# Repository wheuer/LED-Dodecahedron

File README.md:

# LED-Dodecahedron

This repository tracks the most recent state of my LED dodecahedron project.

It's a mess and unpolished. For a more in depth look at the project and it's history see [my website](https://www.williamfheuer.com/project-portfolio).

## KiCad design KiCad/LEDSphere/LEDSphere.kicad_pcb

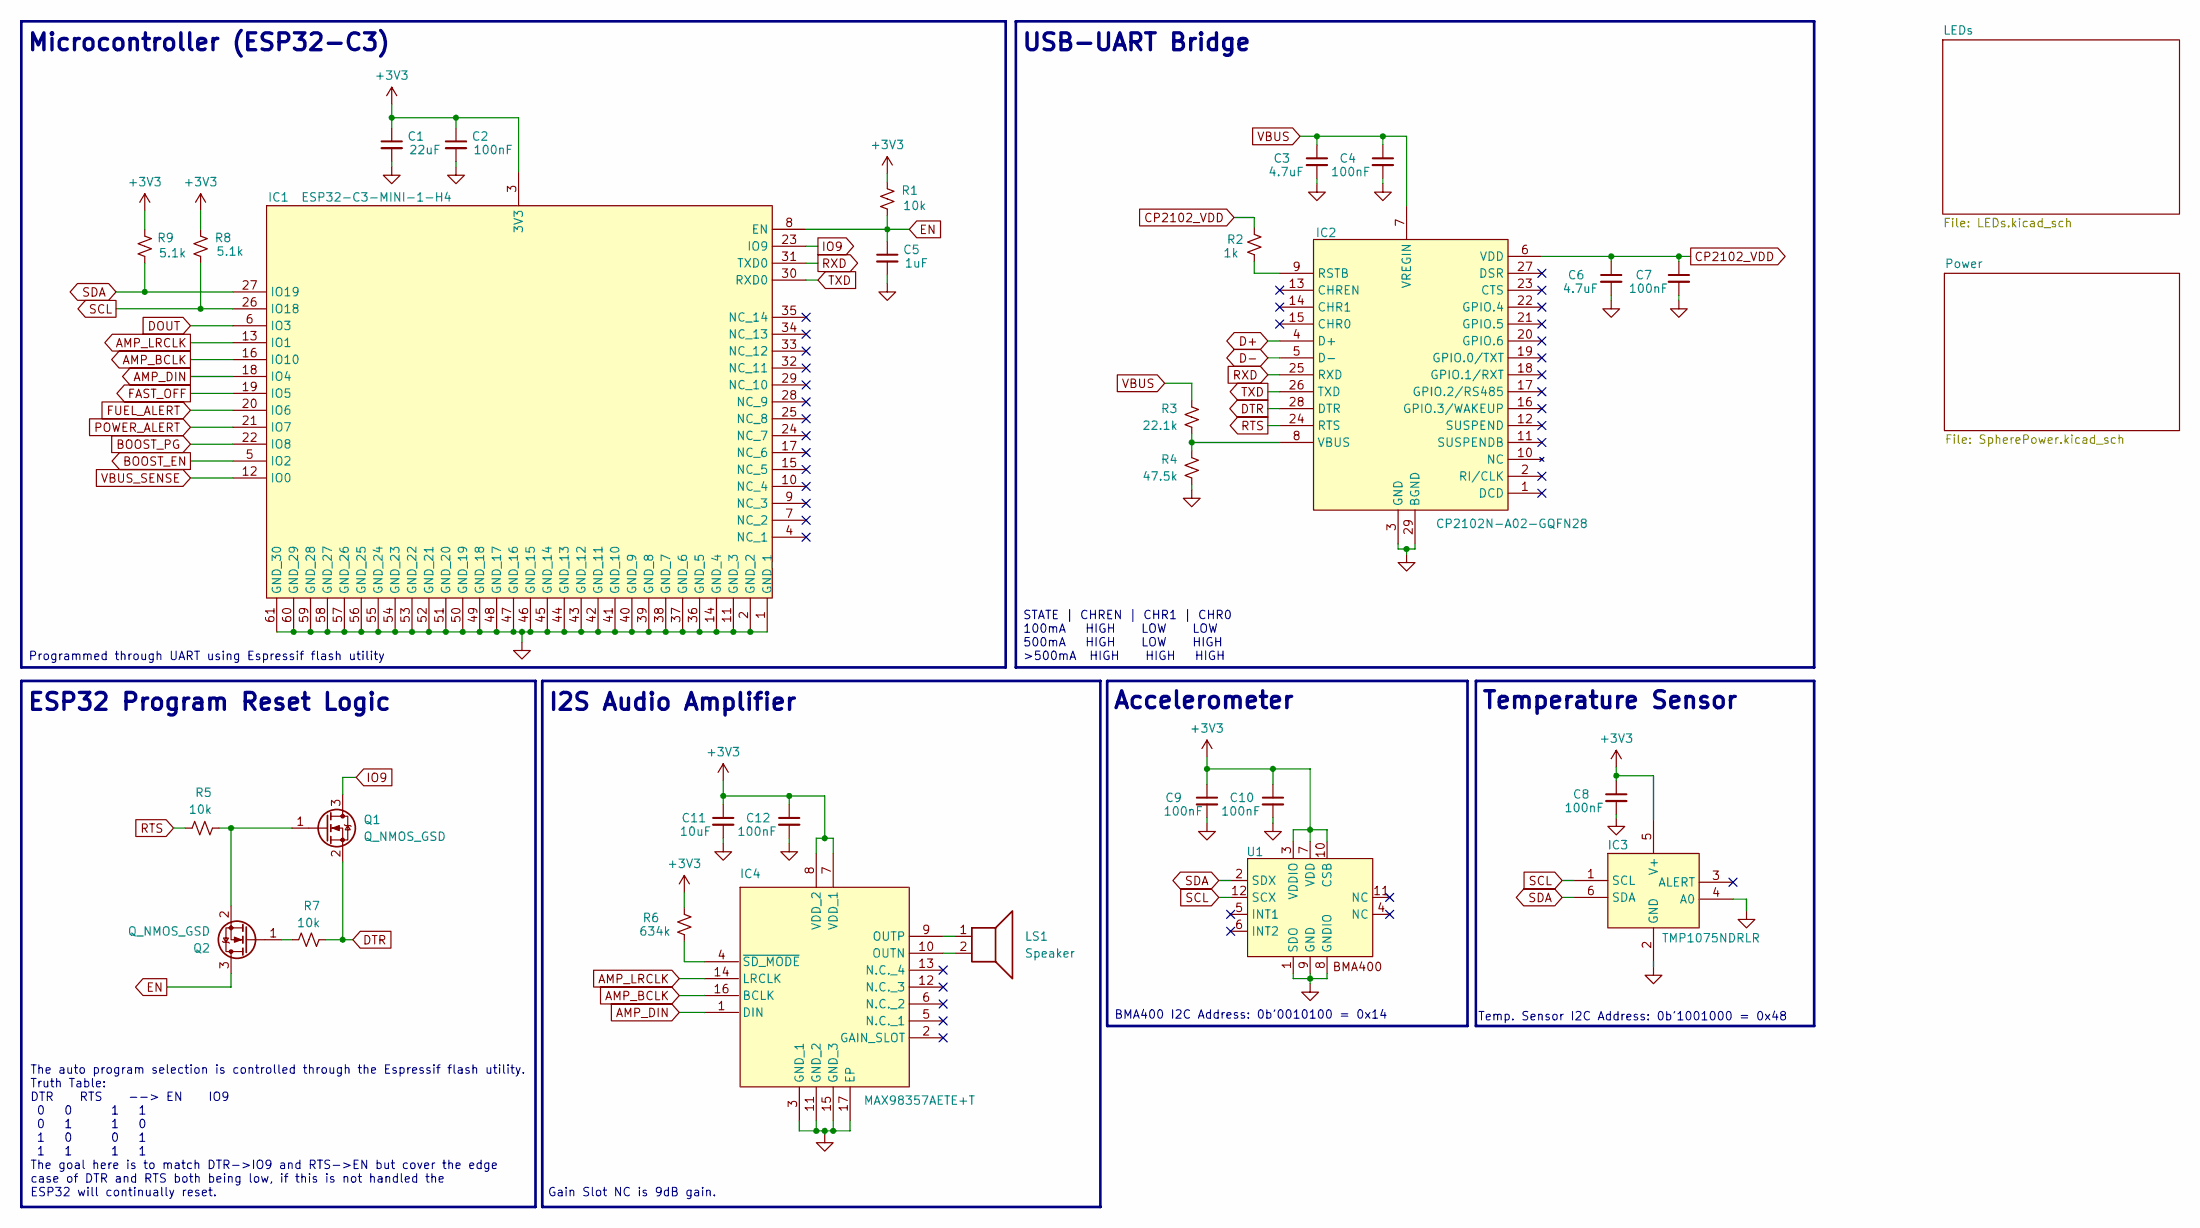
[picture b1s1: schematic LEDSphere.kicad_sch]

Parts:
C1: 22uF; C_0603_1608Metric
C2, C4, C7, C8, C9, C10, C12: 100nF; C_0402_1005Metric
C3, C6: 4.7uF; C_0402_1005Metric
C5: 1uF; C_0402_1005Metric
C11: 10uF; C_0603_1608Metric
IC1: ESP32-C3-MINI-1-H4; ESP32C3MINI1H4; Mouser Part Number 356-ESP32-C3-MINI1H4
IC2: CP2102N-A02-GQFN28; cp2102_QFN50P500X500X80-29N-D; Mouser Part Number 634-CP2102NA02GQFN28
IC3: TMP1075NDRLR; SOTFL50P160X60-6N; Mouser Part Number 595-TMP1075NDRLR
IC4: MAX98357AETE+T; QFN50P300X300X80-17N; Mouser Part Number 700-MAX98357AETE+T
LS1: Speaker; speakerPads
Q1, Q2: Q_NMOS_GSD; NMOS_SOT91P240X110-3N
R1, R5, R7: 10k; R_0402_1005Metric
R2: 1k; R_0402_1005Metric
R3: 22.1k; R_0402_1005Metric
R4: 47.5k; R_0402_1005Metric
R6: 634k; R_0402_1005Metric
R8, R9: 5.1k; R_0402_1005Metric
U1: BOSCH_LGA-12

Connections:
+3V3: C1.1, C2.1, C8.1, C9.1, C10.1, C11.1, C12.1, IC1.3 (3V3), IC3.5 (V+), IC4.7 (VDD_1), IC4.8 (VDD_2), R1.2, R6.2, R8.2, R9.2, U1.3 (VDDIO), U1.7 (VDD), U1.10 (CSB); also elsewhere on the board
AMP_BCLK: IC1.16 (IO10), IC4.16 (BCLK)
AMP_DIN: IC1.18 (IO4), IC4.1 (DIN)
AMP_LRCLK: IC1.13 (IO1), IC4.14 (LRCLK)
BOOST_EN: IC1.5 (IO2); also elsewhere on the board
BOOST_PG: IC1.22 (IO8); also elsewhere on the board
CP2102_VDD: C6.1, C7.1, IC2.6 (VDD), R2.1
D+: IC2.4 (D+); also elsewhere on the board
D-: IC2.5 (D-); also elsewhere on the board
DOUT: IC1.6 (IO3); also elsewhere on the board
DTR: IC2.28 (DTR), Q1.2 (S), R7.1
EN: C5.1, IC1.8 (EN), Q2.3 (D), R1.1
FAST_OFF: IC1.19 (IO5); also elsewhere on the board
FUEL_ALERT: IC1.20 (IO6); also elsewhere on the board
GND: C1.2, C2.2, C3.2, C4.2, C5.2, C6.2, C7.2, C8.2, C9.2, C10.2, C11.2, C12.2, IC1.1 (GND_1), IC1.2 (GND_2), IC1.11 (GND_3), IC1.14 (GND_4), IC1.36 (GND_5), IC1.37 (GND_6), IC1.38 (GND_7), IC1.39 (GND_8), IC1.40 (GND_9), IC1.41 (GND_10), IC1.42 (GND_11), IC1.43 (GND_12), IC1.44 (GND_13), IC1.45 (GND_14), IC1.46 (GND_15), IC1.47 (GND_16), IC1.48 (GND_17), IC1.49 (GND_18), IC1.50 (GND_19), IC1.51 (GND_20), IC1.52 (GND_21), IC1.53 (GND_22), IC1.54 (GND_23), IC1.55 (GND_24), IC1.56 (GND_25), IC1.57 (GND_26), IC1.58 (GND_27), IC1.59 (GND_28), IC1.60 (GND_29), IC1.61 (GND_30), IC2.3 (GND), IC2.29 (BGND), IC3.2 (GND), IC3.4 (A0), IC4.3 (GND_1), IC4.11 (GND_2), IC4.15 (GND_3), IC4.17 (EP), R4.2, U1.1 (SDO), U1.8 (GNDIO), U1.9 (GND); also elsewhere on the board
IO9: IC1.23 (IO9), Q1.3 (D)
unnamed: IC2.9 (RSTB), R2.2
unnamed: IC2.8 (VBUS), R3.2, R4.1
unnamed: IC4.10 (OUTN), LS1.2
unnamed: IC4.9 (OUTP), LS1.1
unnamed: IC4.4 (~SD_MODE), R6.1
unnamed: Q1.1 (G), Q2.2 (S), R5.1
unnamed: Q2.1 (G), R7.2
POWER_ALERT: IC1.21 (IO7); also elsewhere on the board
RTS: IC2.24 (RTS), R5.2
RXD: IC1.31 (TXD0), IC2.25 (RXD)
SCL: IC1.26 (IO18), IC3.1 (SCL), R8.1, U1.12 (SCX); also elsewhere on the board
SDA: IC1.27 (IO19), IC3.6 (SDA), R9.1, U1.2 (SDX); also elsewhere on the board
TXD: IC1.30 (RXD0), IC2.26 (TXD)
VBUS: C3.1, C4.1, IC2.7 (VREGIN), R3.1; also elsewhere on the board
VBUS_SENSE: IC1.12 (IO0); also elsewhere on the board

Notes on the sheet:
I2S Audio Amplifier
Gain Slot NC is 9dB gain.
Temperature Sensor
Microcontroller (ESP32-C3)
Programmed through UART using Espressif flash utility
BMA400 I2C Address: 0b'0010100 = 0x14
The auto program selection is controlled through the Espressif flash utility. Truth Table: DTR RTS --> EN IO9 0 0 1 1 0 1 1 0 1 0 0 1 1 1 1 1 The goal here is to match DTR->IO9 and RTS->EN but cover the edge case of DTR and RTS both being low, if this is not handled the ESP32 will continually reset.
STATE | CHREN | CHR1 | CHR0 100mA HIGH LOW LOW 500mA HIGH LOW HIGH >500mA HIGH HIGH HIGH
Temp. Sensor I2C Address: 0b'1001000 = 0x48
Accelerometer
USB-UART Bridge
ESP32 Program Reset Logic

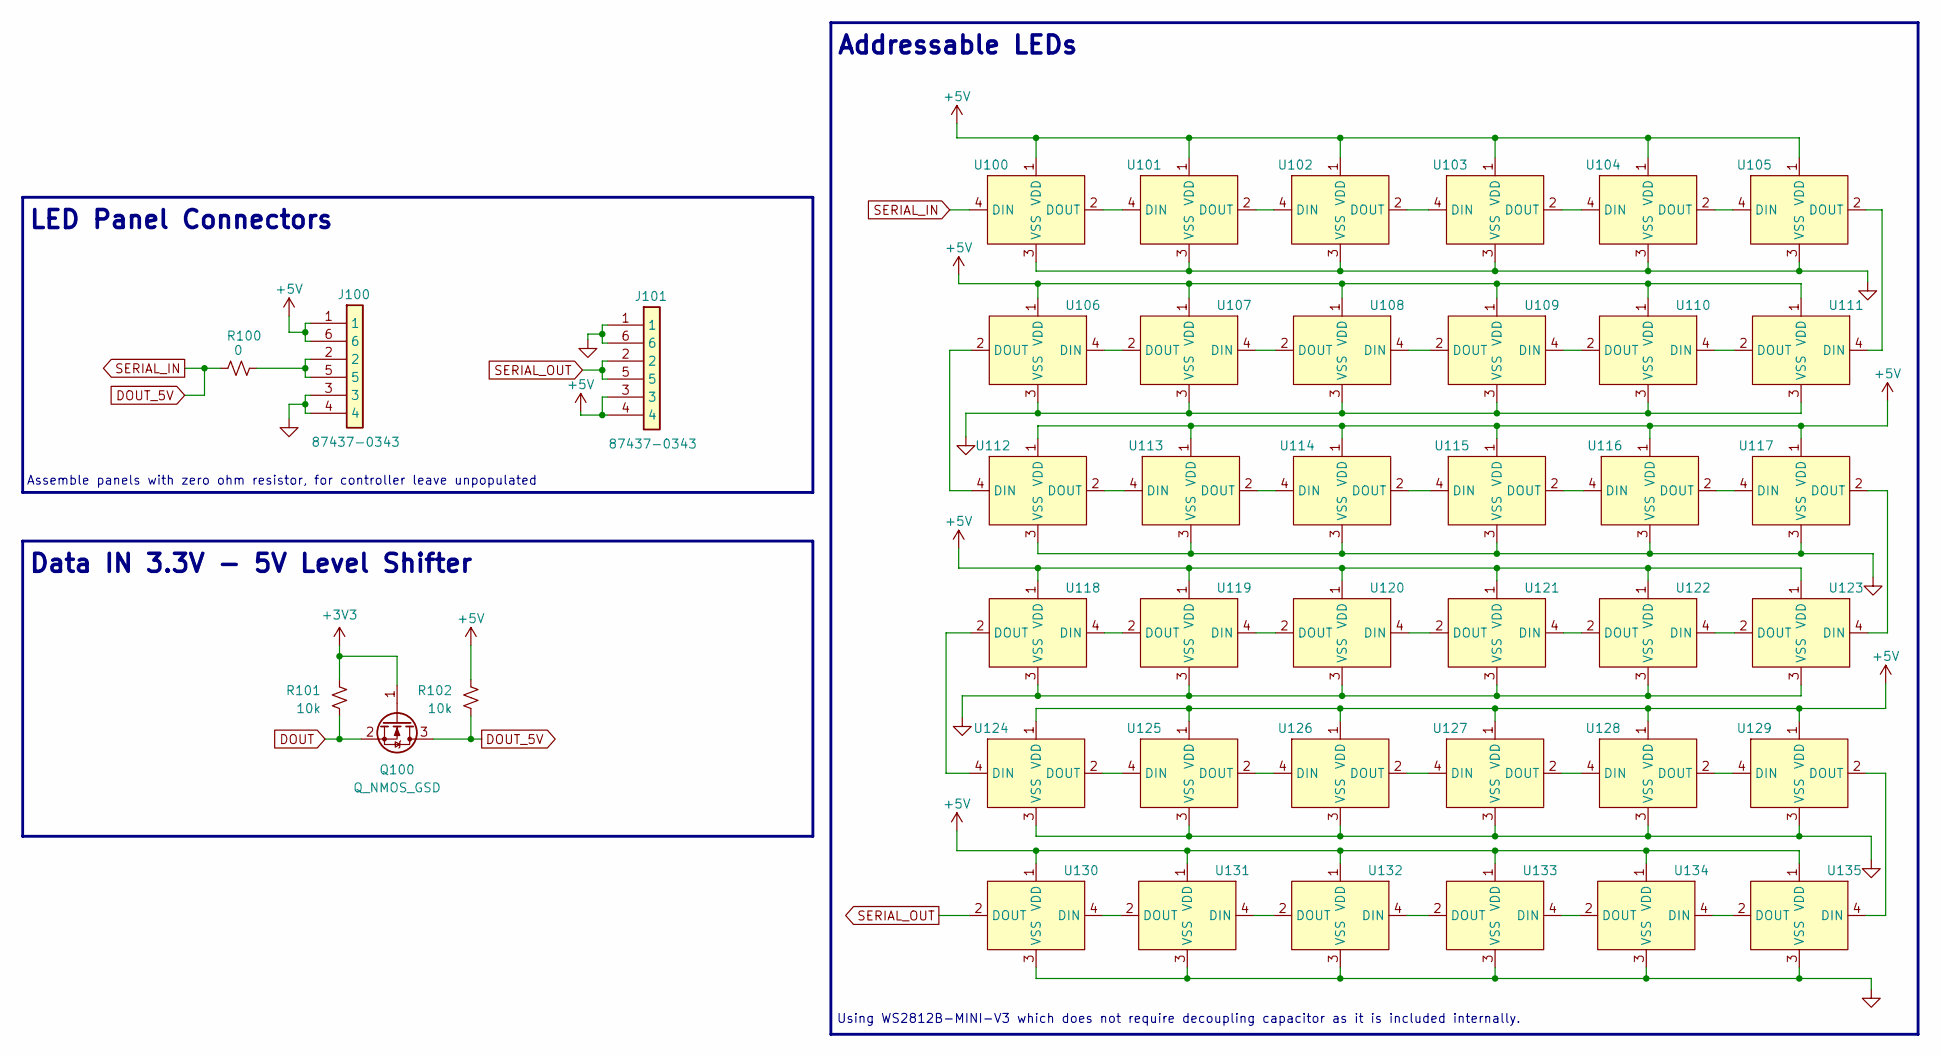
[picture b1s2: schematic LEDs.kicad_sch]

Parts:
J100, J101: 87437-0343; 874370343; Mouser Part Number 538-87437-0343
Q100: Q_NMOS_GSD; NMOS_SOT91P240X110-3N
R100: 0; R_0402_1005Metric
R101, R102: 10k; R_0402_1005Metric
U100, U101, U102, U103, U104, U105, U106, U107, U108, U109, U110, U111, U112, U113, U114, U115, U116, U117, U118, U119, U120, U121, U122, U123, U124, U125, U126, U127, U128, U129, U130, U131, U132, U133, U134, U135: WS2812-W-MINI

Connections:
+3V3: Q100.1 (G), R101.1; also elsewhere on the board
+5V: J100.1, J100.6, J101.3, J101.4, R102.1, U100.1 (VDD), U101.1 (VDD), U102.1 (VDD), U103.1 (VDD), U104.1 (VDD), U105.1 (VDD), U106.1 (VDD), U107.1 (VDD), U108.1 (VDD), U109.1 (VDD), U110.1 (VDD), U111.1 (VDD), U112.1 (VDD), U113.1 (VDD), U114.1 (VDD), U115.1 (VDD), U116.1 (VDD), U117.1 (VDD), U118.1 (VDD), U119.1 (VDD), U120.1 (VDD), U121.1 (VDD), U122.1 (VDD), U123.1 (VDD), U124.1 (VDD), U125.1 (VDD), U126.1 (VDD), U127.1 (VDD), U128.1 (VDD), U129.1 (VDD), U130.1 (VDD), U131.1 (VDD), U132.1 (VDD), U133.1 (VDD), U134.1 (VDD), U135.1 (VDD); also elsewhere on the board
DOUT: Q100.2 (S), R101.2; also elsewhere on the board
DOUT_5V: Q100.3 (D), R100.1, R102.2, U100.4 (DIN)
GND: J100.3, J100.4, J101.1, J101.6, U100.3 (VSS), U101.3 (VSS), U102.3 (VSS), U103.3 (VSS), U104.3 (VSS), U105.3 (VSS), U106.3 (VSS), U107.3 (VSS), U108.3 (VSS), U109.3 (VSS), U110.3 (VSS), U111.3 (VSS), U112.3 (VSS), U113.3 (VSS), U114.3 (VSS), U115.3 (VSS), U116.3 (VSS), U117.3 (VSS), U118.3 (VSS), U119.3 (VSS), U120.3 (VSS), U121.3 (VSS), U122.3 (VSS), U123.3 (VSS), U124.3 (VSS), U125.3 (VSS), U126.3 (VSS), U127.3 (VSS), U128.3 (VSS), U129.3 (VSS), U130.3 (VSS), U131.3 (VSS), U132.3 (VSS), U133.3 (VSS), U134.3 (VSS), U135.3 (VSS); also elsewhere on the board
unnamed: J100.2, J100.5, R100.2
unnamed: U100.2 (DOUT), U101.4 (DIN)
unnamed: U101.2 (DOUT), U102.4 (DIN)
unnamed: U102.2 (DOUT), U103.4 (DIN)
unnamed: U103.2 (DOUT), U104.4 (DIN)
unnamed: U104.2 (DOUT), U105.4 (DIN)
unnamed: U105.2 (DOUT), U111.4 (DIN)
unnamed: U106.4 (DIN), U107.2 (DOUT)
unnamed: U106.2 (DOUT), U112.4 (DIN)
unnamed: U107.4 (DIN), U108.2 (DOUT)
unnamed: U108.4 (DIN), U109.2 (DOUT)
unnamed: U109.4 (DIN), U110.2 (DOUT)
unnamed: U110.4 (DIN), U111.2 (DOUT)
unnamed: U112.2 (DOUT), U113.4 (DIN)
unnamed: U113.2 (DOUT), U114.4 (DIN)
unnamed: U114.2 (DOUT), U115.4 (DIN)
unnamed: U115.2 (DOUT), U116.4 (DIN)
unnamed: U116.2 (DOUT), U117.4 (DIN)
unnamed: U117.2 (DOUT), U123.4 (DIN)
unnamed: U118.4 (DIN), U119.2 (DOUT)
unnamed: U118.2 (DOUT), U124.4 (DIN)
unnamed: U119.4 (DIN), U120.2 (DOUT)
unnamed: U120.4 (DIN), U121.2 (DOUT)
unnamed: U121.4 (DIN), U122.2 (DOUT)
unnamed: U122.4 (DIN), U123.2 (DOUT)
unnamed: U124.2 (DOUT), U125.4 (DIN)
unnamed: U125.2 (DOUT), U126.4 (DIN)
unnamed: U126.2 (DOUT), U127.4 (DIN)
unnamed: U127.2 (DOUT), U128.4 (DIN)
unnamed: U128.2 (DOUT), U129.4 (DIN)
unnamed: U129.2 (DOUT), U135.4 (DIN)
unnamed: U130.4 (DIN), U131.2 (DOUT)
unnamed: U131.4 (DIN), U132.2 (DOUT)
unnamed: U132.4 (DIN), U133.2 (DOUT)
unnamed: U133.4 (DIN), U134.2 (DOUT)
unnamed: U134.4 (DIN), U135.2 (DOUT)
SERIAL_OUT: J101.2, J101.5, U130.2 (DOUT)

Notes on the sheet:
LED Panel Connectors
Addressable LEDs
Data IN 3.3V - 5V Level Shifter
Assemble panels with zero ohm resistor, for controller leave unpopulated
Using WS2812B-MINI-V3 which does not require decoupling capacitor as it is included internally.

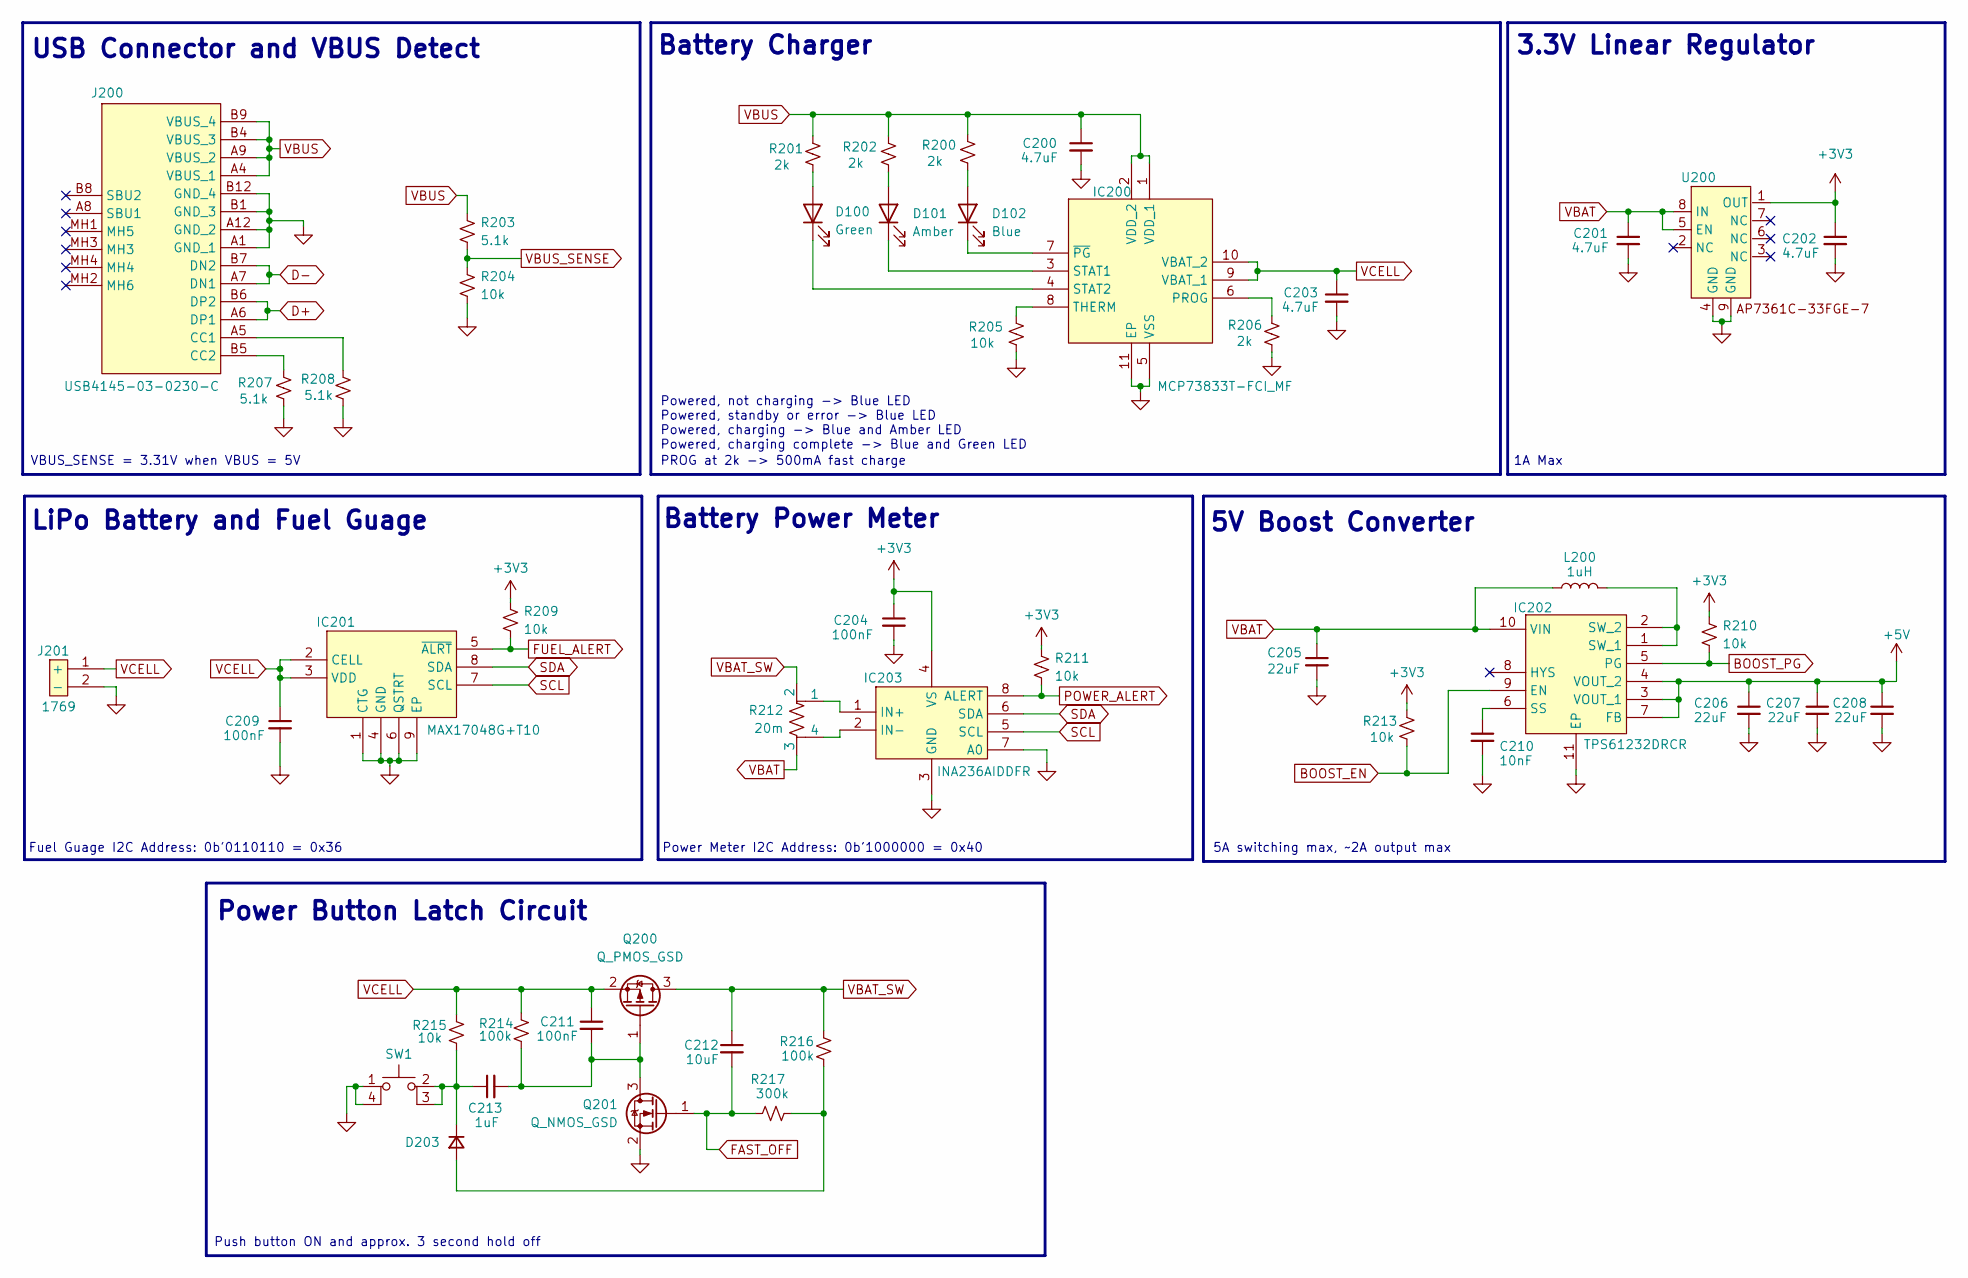
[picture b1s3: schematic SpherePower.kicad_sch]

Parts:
C200, C201, C202, C203: 4.7uF; C_0402_1005Metric
C204, C209, C211: 100nF; C_0402_1005Metric
C205, C206, C207, C208: 22uF; C_0603_1608Metric
C210: 10nF; C_0402_1005Metric
C212: 10uF; C_0603_1608Metric
C213: 1uF; C_0402_1005Metric
D100: Green; LED_0402_1005Metric
D101: Amber; LED_0402_1005Metric
D102: Blue; LED_0402_1005Metric
D203: D_Small; D_SOD-123F
IC200: MCP73833T-FCI_MF; batteryChg_SON50P300X300X100-11N-D; Mouser Part Number 579-MCP73833T-FCI/MF
IC201: MAX17048G+T10; SON50P200X200X80-9N-D; Mouser Part Number 700-MAX17048G+T10
IC202: TPS61232DRCR; boost_SON50P300X300X100-11N-D; Mouser Part Number 595-TPS61232DRCR
IC203: INA236AIDDFR; SOP65P280X110-8N; Mouser Part Number 595-INA236AIDDFR
J200: USB4145-03-0230-C; vertical_USB4145030230C; Mouser Part Number 640-USB4145-3-0230-C
J201: 1769; Mouser Part Number 485-1769
L200: 1uH; boostInductor_XFL4020
Q200: Q_PMOS_GSD; SSM3J332RLFT
Q201: Q_NMOS_GSD; NMOS_SOT91P240X110-3N
R200, R201, R202, R206: 2k; R_0402_1005Metric
R203, R207, R208: 5.1k; R_0402_1005Metric
R204, R205, R209, R210, R211, R213, R215: 10k; R_0402_1005Metric
R212: 20m; shunt_LVK12R020DER
R214, R216: 100k; R_0402_1005Metric
R217: 300k; R_0402_1005Metric
SW1: button_KMR_2
U200: linearReg_SON65P300X300X63-9N

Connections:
+3V3: C202.1, C204.1, IC203.4 (VS), R209.2, R210.2, R211.2, R213.2, U200.1 (OUT); also elsewhere on the board
+5V: C206.1, C207.1, C208.1, IC202.3 (VOUT_1), IC202.4 (VOUT_2), IC202.7 (FB); also elsewhere on the board
BOOST_EN: IC202.9 (EN), R213.1; also elsewhere on the board
BOOST_PG: IC202.5 (PG), R210.1; also elsewhere on the board
D+: J200.A6 (DP1), J200.B6 (DP2); also elsewhere on the board
D-: J200.A7 (DN1), J200.B7 (DN2); also elsewhere on the board
FAST_OFF: C212.2, Q201.1 (G), R217.2; also elsewhere on the board
FUEL_ALERT: IC201.5 (~ALRT), R209.1; also elsewhere on the board
GND: C200.2, C201.2, C202.2, C203.2, C204.2, C205.2, C206.2, C207.2, C208.2, C209.2, C210.2, IC200.5 (VSS), IC200.11 (EP), IC201.1 (CTG), IC201.4 (GND), IC201.6 (QSTRT), IC201.9 (EP), IC202.11 (EP), IC203.3 (GND), IC203.7 (A0), J200.A1 (GND_1), J200.A12 (GND_2), J200.B1 (GND_3), J200.B12 (GND_4), J201.2 (-), Q201.2 (S), R204.1, R205.1, R206.1, R207.1, R208.1, SW1.1, SW1.4, U200.4 (GND), U200.9 (GND); also elsewhere on the board
unnamed 18: R201.1; also elsewhere on the board
unnamed 19: IC200.4 (STAT2); also elsewhere on the board
unnamed 20: R202.1; also elsewhere on the board
unnamed 21: IC200.3 (STAT1); also elsewhere on the board
unnamed 22: R200.1; also elsewhere on the board
unnamed 23: IC200.7 (~PG); also elsewhere on the board
unnamed: D203.2 (A), R216.1, R217.1
unnamed: C213.1, D203.1 (K), R215.1, SW1.2, SW1.3
unnamed: IC200.6 (PROG), R206.2
unnamed: IC200.8 (THERM), R205.2
unnamed: C210.1, IC202.6 (SS)
unnamed: IC202.1 (SW_1), IC202.2 (SW_2), L200.2
unnamed: IC203.1 (IN+), R212.1
unnamed: IC203.2 (IN-), R212.4
unnamed: J200.A5 (CC1), R208.2
unnamed: J200.B5 (CC2), R207.2
unnamed: C211.2, C213.2, Q200.1 (G), Q201.3 (D), R214.1
POWER_ALERT: IC203.8 (ALERT), R211.1; also elsewhere on the board
SCL: IC201.7 (SCL), IC203.5 (SCL); also elsewhere on the board
SDA: IC201.8 (SDA), IC203.6 (SDA); also elsewhere on the board
VBAT: C201.1, C205.1, IC202.10 (VIN), L200.1, R212.3, U200.5 (EN), U200.8 (IN)
VBAT_SW: C212.1, Q200.3 (D), R212.2, R216.2
VBUS: C200.1, IC200.1 (VDD_1), IC200.2 (VDD_2), J200.A4 (VBUS_1), J200.A9 (VBUS_2), J200.B4 (VBUS_3), J200.B9 (VBUS_4), R200.2, R201.2, R202.2, R203.2; also elsewhere on the board
VBUS_SENSE: R203.1, R204.2; also elsewhere on the board
VCELL: C203.1, C209.1, C211.1, IC200.9 (VBAT_1), IC200.10 (VBAT_2), IC201.2 (CELL), IC201.3 (VDD), J201.1 (+), Q200.2 (S), R214.2, R215.2

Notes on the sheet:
USB Connector and VBUS Detect
Fuel Guage I2C Address: 0b'0110110 = 0x36
5A switching max, ~2A output max
LiPo Battery and Fuel Guage
Powered, not charging -> Blue LED Powered, standby or error -> Blue LED Powered, charging -> Blue and Amber LED Powered, charging complete -> Blue and Green LED
5V Boost Converter
3.3V Linear Regulator
VBUS_SENSE = 3.31V when VBUS = 5V
Power Meter I2C Address: 0b'1000000 = 0x40
Battery Charger
Power Button Latch Circuit
PROG at 2k -> 500mA fast charge
Battery Power Meter
Push button ON and approx. 3 second hold off
1A Max

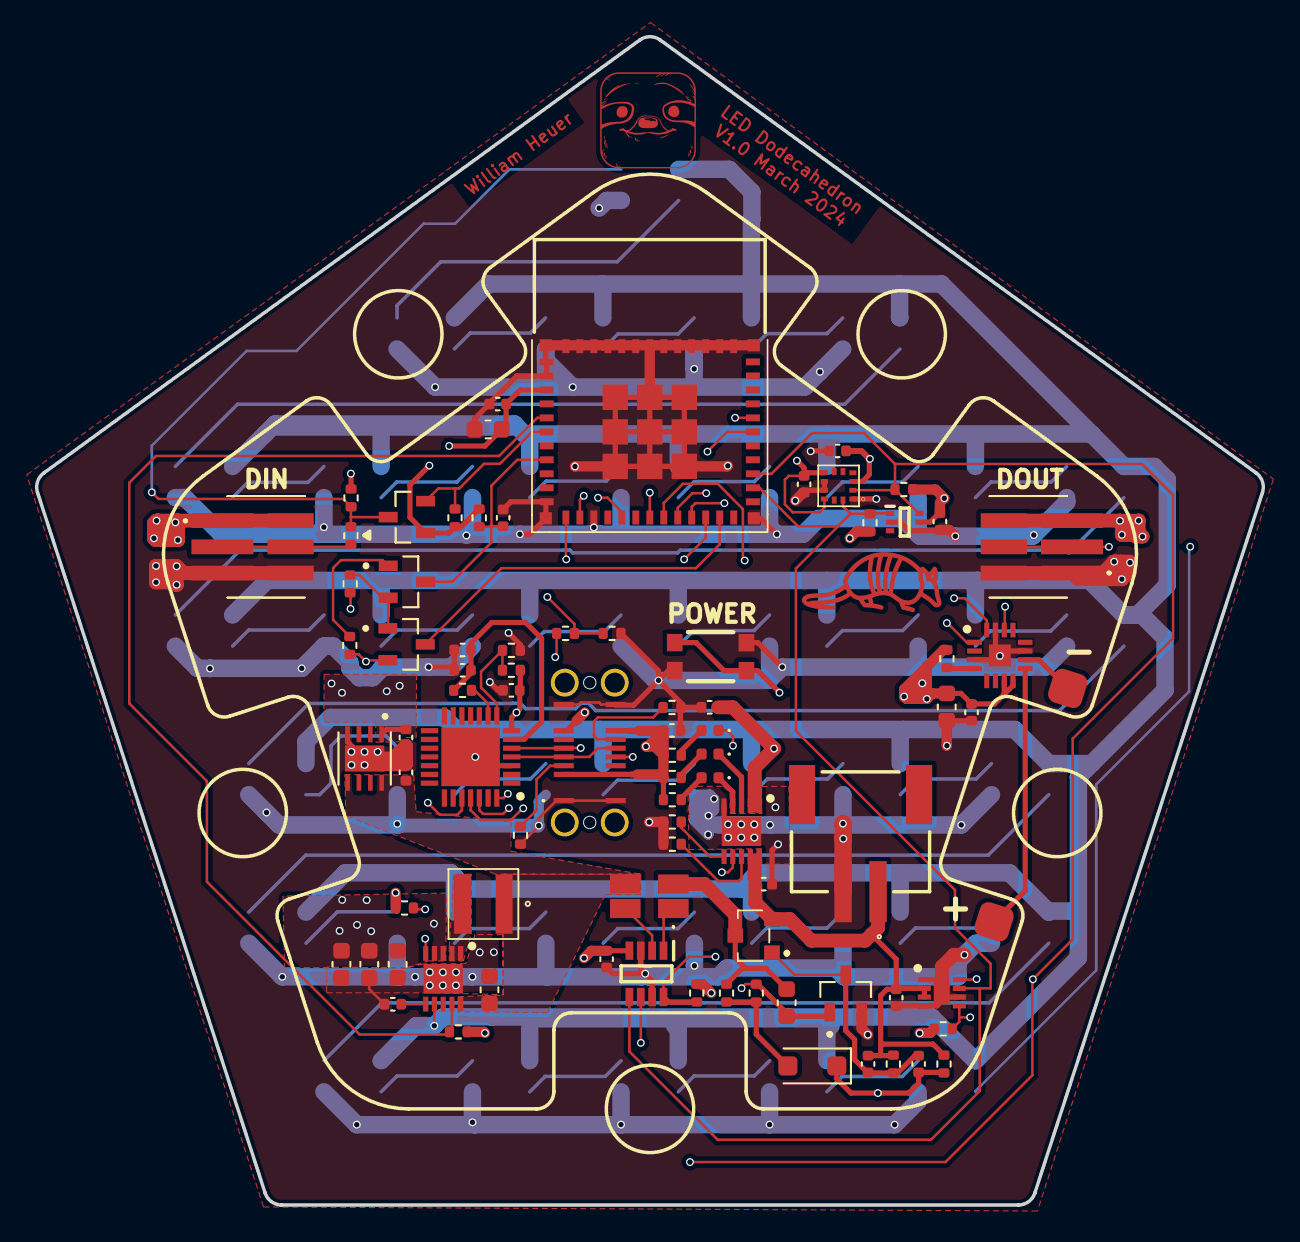
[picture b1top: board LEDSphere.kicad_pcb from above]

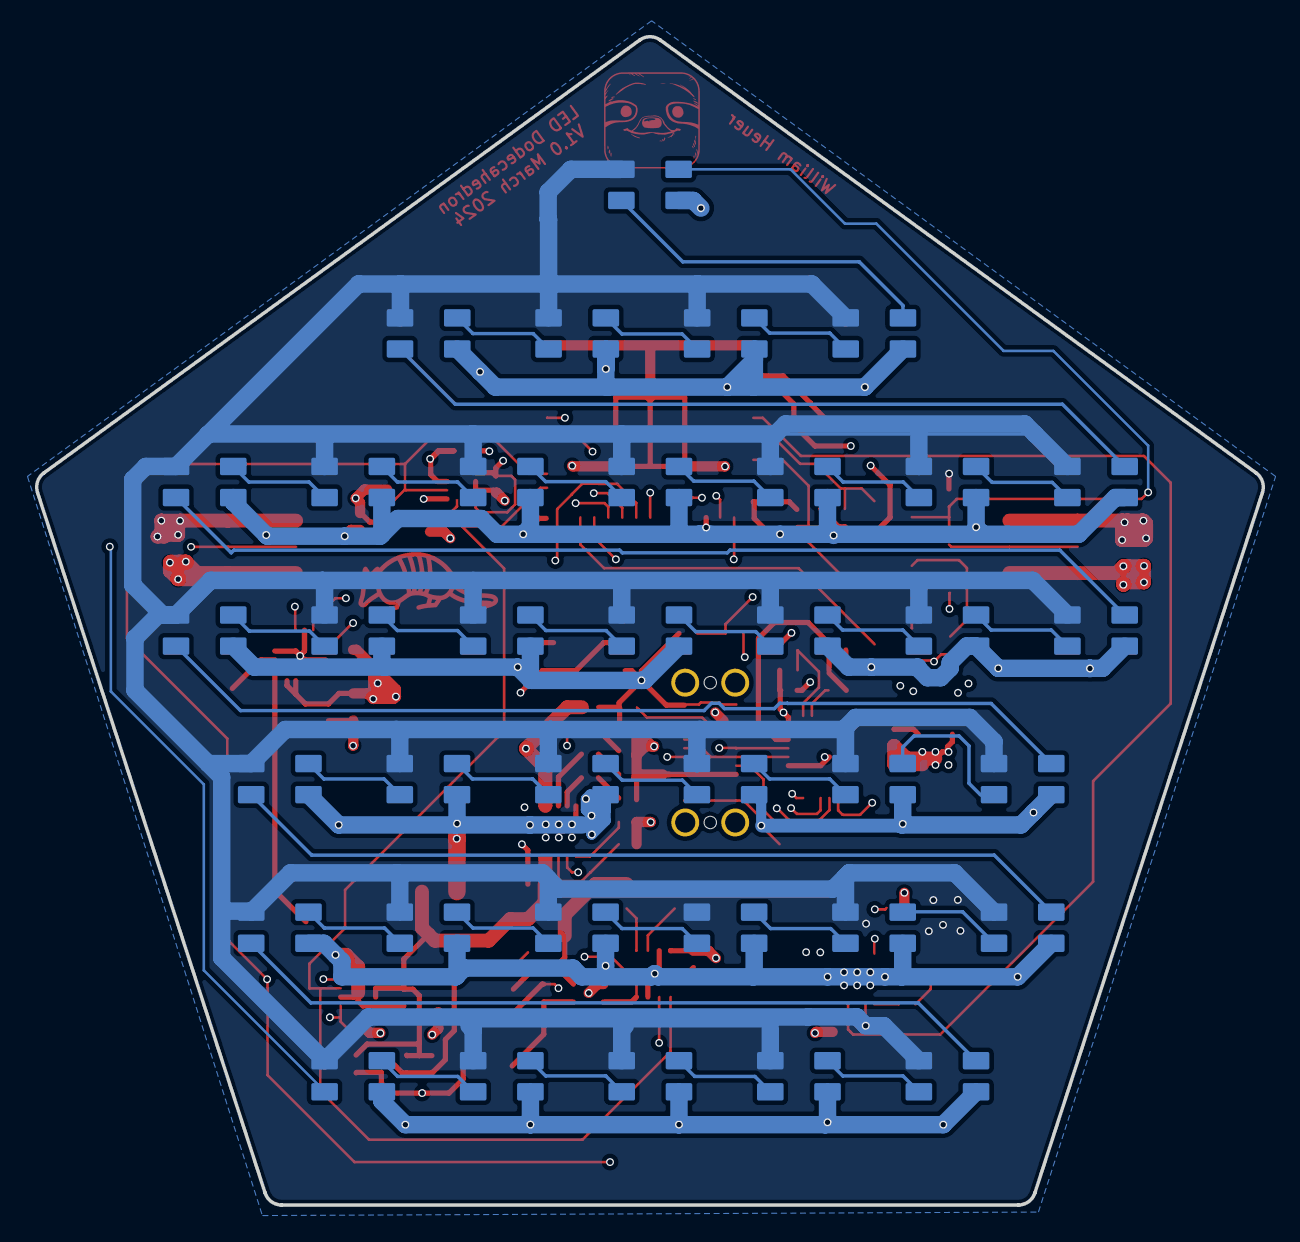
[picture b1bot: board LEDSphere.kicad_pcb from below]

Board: 4 copper layers, 70.2 x 66.8 mm, 118 parts (36 on the bottom side), 90 nets.

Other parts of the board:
D200: Green; LED_0402_1005Metric
D201: Amber; LED_0402_1005Metric
D202: Blue; LED_0402_1005Metric

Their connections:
unnamed 18: D200.2 (A); also elsewhere on the board
unnamed 19: D200.1 (K); also elsewhere on the board
unnamed 20: D201.2 (A); also elsewhere on the board
unnamed 21: D201.1 (K); also elsewhere on the board
unnamed 22: D202.2 (A); also elsewhere on the board
unnamed 23: D202.1 (K); also elsewhere on the board

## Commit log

2025-01-10 [Firmware] Fuel gauge and temp sensor MVP's complete
2025-01-12 [Firmware] Minimum LED and power meter MVP complete
2025-01-16 [Firmware] Main system loop coming along, almost at total MVP. Still an issue with switching to and from NONE effect
2025-03-07 General sync before polishing
2025-03-08 Update datasheets and minimal README
2025-03-27 [Effect Tweaks] Slow down default effect FPS and update README.
